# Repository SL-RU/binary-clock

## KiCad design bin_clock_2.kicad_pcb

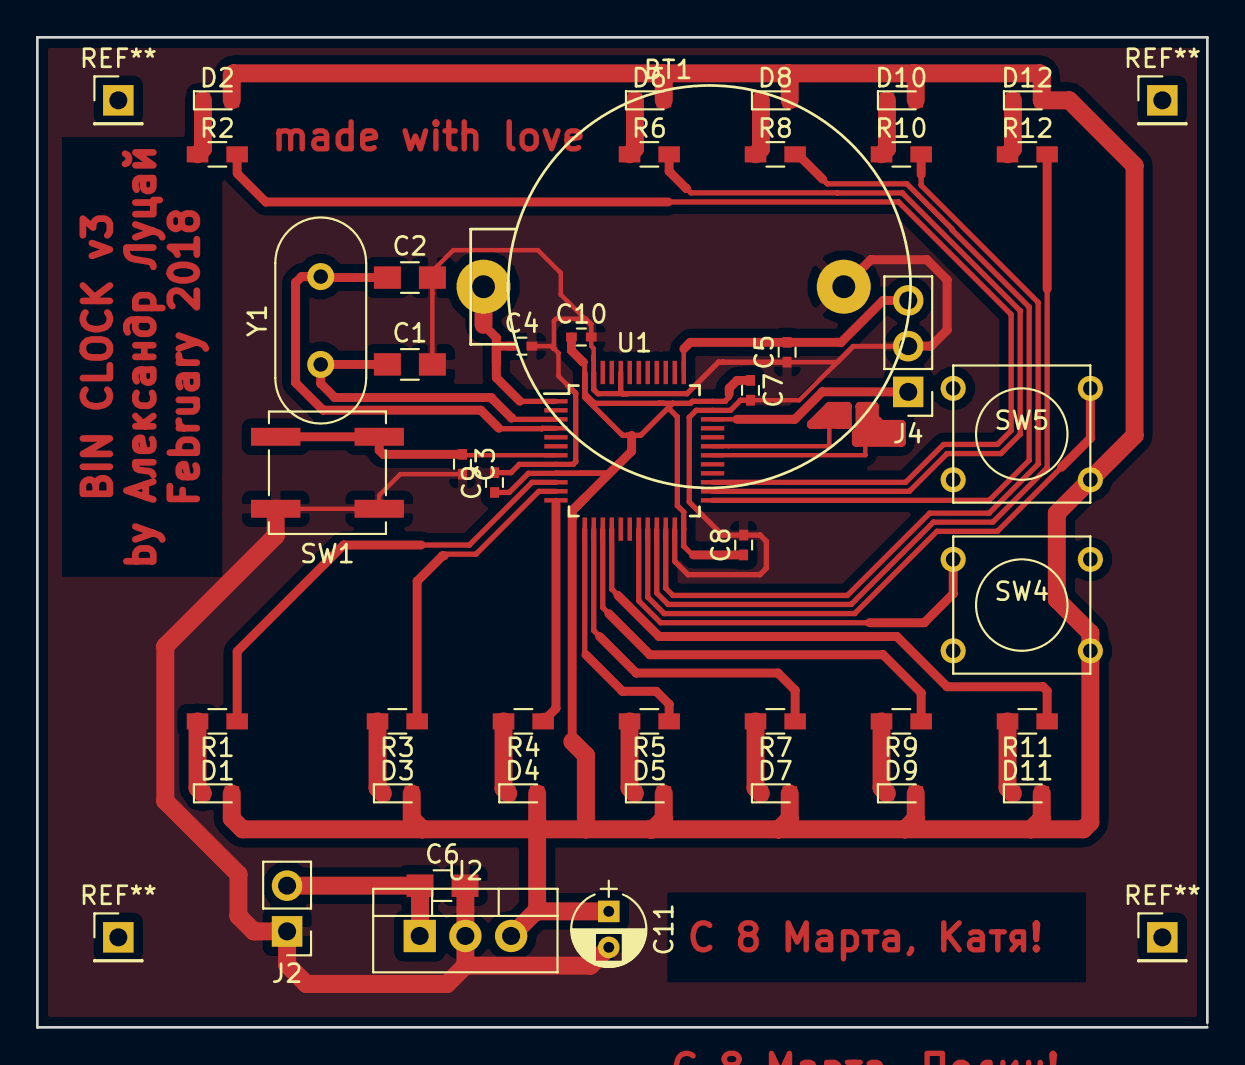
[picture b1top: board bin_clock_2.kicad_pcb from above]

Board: 2 copper layers, 65.0 x 55.0 mm, 44 parts (0 on the bottom side), 35 nets.

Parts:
BT1: cr2032; BS-7_CR2032
C1, C2: 14pF; C_0805_HandSoldering
C3, C4, C7, C8, C9, C10: 0.1uF; C_0402
C5: 1nF; C_0402
C6: 10uF; C_0805_HandSoldering
C11: 100uF; CP_Radial_D4.0mm_P2.00mm
D1, D2, D3, D4, D5, D6, D7, D8, D9, D10, D11, D12: LED; LED_0603
J2: power; Pin_Header_Straight_1x02_Pitch2.54mm
J4: swd; Pin_Header_Straight_1x03_Pitch2.54mm
R1, R2, R3, R4, R5, R6, R7, R8, R9, R10, R11, R12: 330; R_0603_HandSoldering
SW1: SW_Push; SW_SPST_B3SL-1002P
SW4, SW5: SW_Push; SW_PUSH_SMALL
U1: STM32F103C8Tx; LQFP-48_7x7mm_Pitch0.5mm
U2: LM7805CT; TO-220_Vertical
Y1: Crystal; Crystal_HC49-4H_Vertical

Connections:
+3V3: C7.1, C8.1, C9.1, C10.1, C11.1, D1.2, D2.2, D3.2, D4.2, D5.2, D6.2, D7.2, D8.2, D9.2, D10.2, D11.2, D12.2, SW4.2, SW5.2, U1.9, U1.24, U1.36, U1.48, U2.3
/PM: R2.2, U1.27
/SEC: R1.1, U1.10
/b3: SW4.1, U1.19
/b4: SW5.1, U1.20
/h1: R12.2, U1.21
/h2: R10.2, U1.22
/h4: R8.2, U1.25
/h8: R6.2, U1.26
/m1: R11.1, U1.16
/m2: R9.1, U1.15
/m4: R7.1, U1.14
/m8: R5.1, U1.13
/m16: R4.1, U1.12
/m32: R3.1, U1.11
GND: BT1.2, C1.2, C2.2, C3.2, C4.2, C5.1, C6.2, C7.2, C8.2, C9.2, C10.2, C11.2, J2.1, J4.2, SW1.1, U1.8, U1.23, U1.35, U1.44, U1.47, U2.2
unnamed: BT1.1, C4.1, U1.1
unnamed: C1.1, U1.3, Y1.1
unnamed: C2.1, U1.4, Y1.2
unnamed: C3.1, SW1.2, U1.7
unnamed: C5.2, J4.3, U1.37
unnamed: C6.1, J2.2, U2.1
unnamed: D1.1, R1.2
unnamed: D2.1, R2.1
unnamed: D3.1, R3.2
unnamed: D4.1, R4.2
unnamed: D5.1, R5.2
unnamed: D6.1, R6.1
unnamed: D7.1, R7.2
unnamed: D8.1, R8.1
unnamed: D9.1, R9.2
unnamed: D10.1, R10.1
unnamed: D11.1, R11.2
unnamed: D12.1, R12.1
unnamed: J4.1, U1.34

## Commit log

2017-04-13 first
2017-05-11 done
2017-05-11 pcb ready
2018-02-28 smallest clock
2018-03-08 front
2018-03-08 front fix
